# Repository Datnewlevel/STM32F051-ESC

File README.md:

# Single ESC

An open-source hardware learning project for a three-phase electronic speed controller (ESC), designed in KiCad. I created this schematic and PCB while studying existing ESC circuits shared online to understand how their power supply, gate driver, motor bridge, and sensing stages work together.

This is the first PCB revision. I am currently ordering the board for fabrication; the hardware has not yet been assembled or tested.

---

## 1. Overview

The design combines a microcontroller, a three-phase gate driver, six power MOSFETs, and voltage and current sensing on a four-layer PCB. The schematic labels the intended battery input range as 14-25 V. This range is a design target, not a verified operating specification.

The main parts are:

| Function | Component |
|---|---|
| Microcontroller | STM32F051K8U7 |
| Three-phase gate driver | DRV8300DPWR |
| Motor bridge | Six PSMN1R4-40YLDX-VB MOSFETs |
| 3.3 V and 12 V supplies | Two TPS62932DRLR buck converters |
| Current measurement | INA180B2IDBVT amplifier and a 1 mΩ shunt |

The schematic also includes back-EMF sensing for the three motor phases, SWD programming pads, a signal input, telemetry connections, and test pads.

---

## 2. Schematic

The full schematic is available as a [PDF](ESC_PCB/test.pdf). It is divided into the power supplies, microcontroller, gate driver, back-EMF sensing, MOSFET bridge, connectors, and current-sensing sections.

---

## 3. PCB Design

The board is approximately 66.05 × 61.80 mm, with four copper layers and a 1.6 mm board thickness in the KiCad project.

### Top Layer

### GND Plane (Inner Layer 1)

### PWR Plane (Inner Layer 2)

### Bottom Layer

### 3D View

---

## 4. Project Files

| File / Folder | Description |
|---|---|
| `test.kicad_pro` | Main KiCad project settings |
| `test.kicad_sch` | Single ESC schematic source |
| `test.kicad_pcb` | Four-layer PCB layout source |
| `ESC_PCB/` | Schematic PDF and PCB images |
| `production/bom.csv` | Generated bill of materials |
| `production/positions.csv` | Generated component placement data |
| `production/designators.csv` | Generated designator list |
| `production/netlist.ipc` | Generated IPC netlist |
| `production/test.zip` | Generated Gerber and drill files |
| `test/` | A separate KiCad experiment; it is not part of the ESC design |

---

## 5. Current Status

The PCB is being ordered for the first prototype. Assembly, power-up checks, firmware, and motor testing are still pending. The design and fabrication files are shared for study and review, but the board should not be treated as a tested ESC.

---

## 6. References and Open Source

I drew this circuit while referring to existing ESC schematics and other circuits available on the internet. Those references helped me learn the operating principles of an ESC. I do not claim that every circuit idea in this design is original. Specific source links have not yet been collected; I will add attribution for identifiable references.

I intend to release the complete hardware project as open-source hardware. A formal license has not yet been selected and will be added before the public release.

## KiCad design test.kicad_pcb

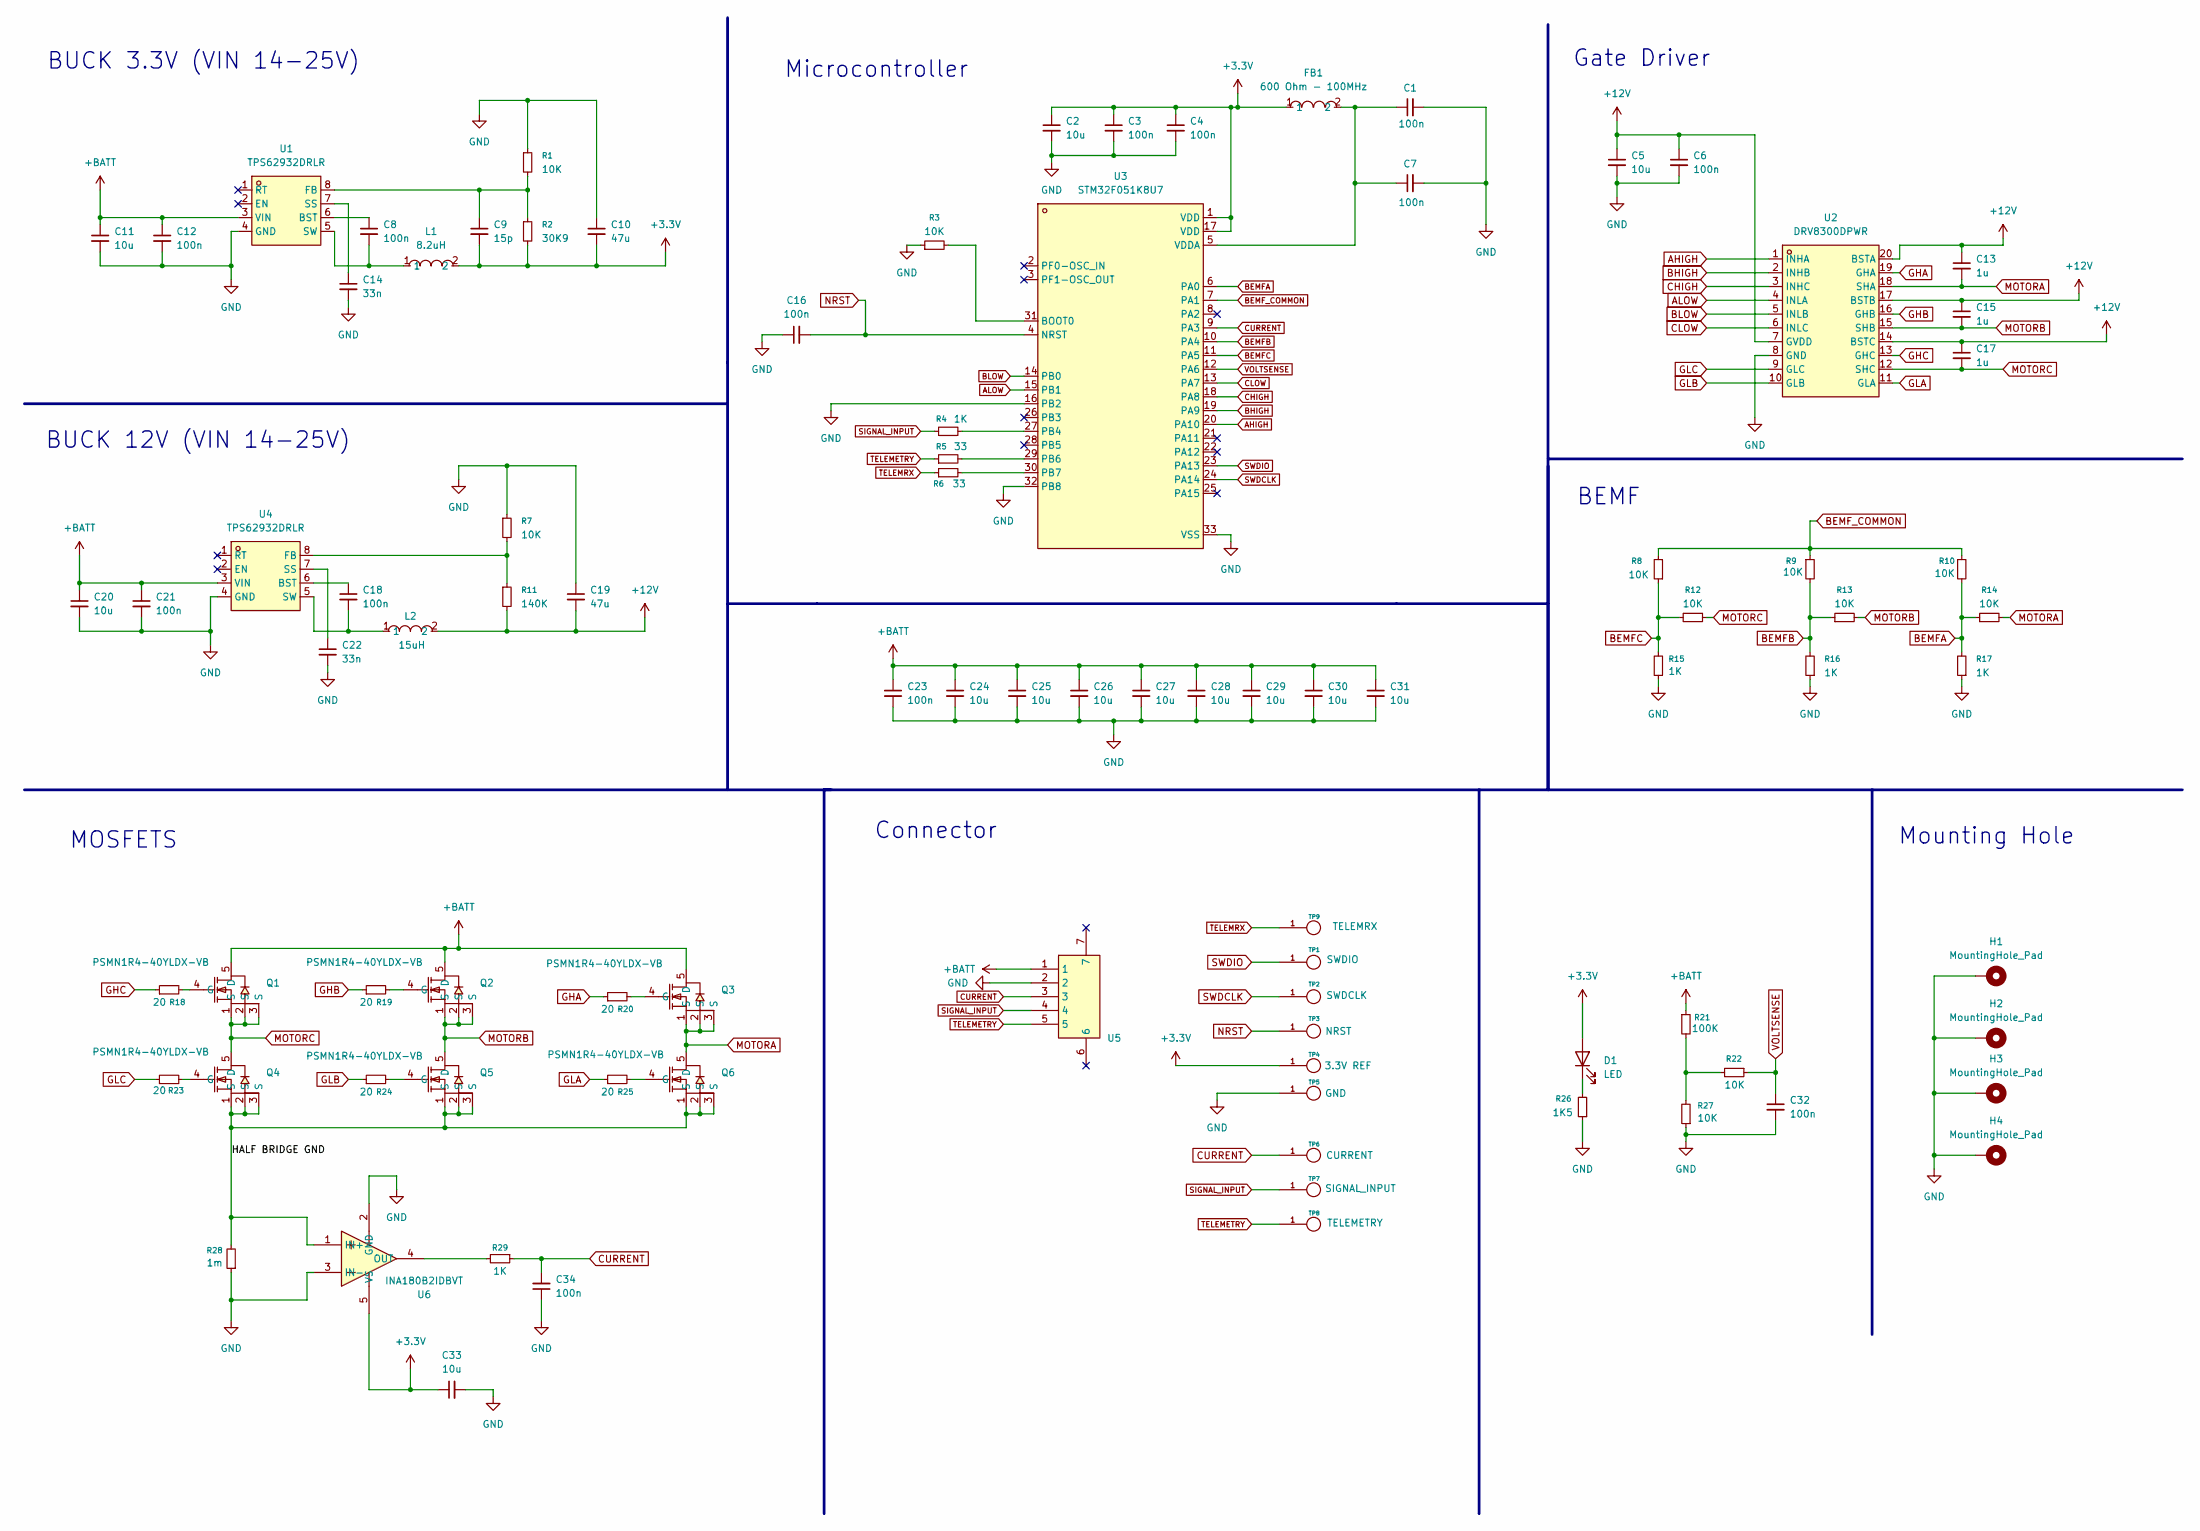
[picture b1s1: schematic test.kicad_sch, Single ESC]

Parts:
C1, C3, C4, C6, C7, C8, C12, C16, C18, C21, C32, C34: 100n; C_0805_2012Metric_Pad1.18x1.45mm_HandSolder
C2, C5, C11, C20, C33: 10u; C_0805_2012Metric_Pad1.18x1.45mm_HandSolder
C9: 15p; C_0805_2012Metric_Pad1.18x1.45mm_HandSolder
C10, C19: 47u; C_1210_3225Metric_Pad1.33x2.70mm_HandSolder
C13, C15, C17: 1u; C_0805_2012Metric_Pad1.18x1.45mm_HandSolder
C14, C22: 33n; C_0805_2012Metric_Pad1.18x1.45mm_HandSolder
C23: 100n; C_1210_3225Metric_Pad1.33x2.70mm_HandSolder
C24, C25, C26, C27, C28, C29, C30, C31: 10u; C_1210_3225Metric_Pad1.33x2.70mm_HandSolder
D1: LED; LED_0805_2012Metric_Pad1.15x1.40mm_HandSolder; LCSC Part C84256
FB1: 600 Ohm - 100MHz; L0603; MPN BLM18KG601SN1D; LCSC Part C85833
H1, H2, H3, H4: MountingHole_Pad; MountingHole_3.2mm_M3_Pad
L1: 8.2uH; IND-SMD_L7.1-W6.6; MPN PSPMAA0603-8R2M-ANF; LCSC Part C436550
L2: 15uH; IND-SMD_L7.1-W6.6; MPN MDA7030-150M; LCSC Part C2847486
Q1, Q2, Q3, Q4, Q5, Q6: PSMN1R4-40YLDX-VB; LFPAK56-4_L4.9-W4.2-P1.27-LS6.2-BL; MPN PSMN1R4-40YLDX-VB; LCSC Part C49253744
R1, R3, R7, R8, R9, R10, R12, R13, R14, R22, R27: 10K; R_0805_2012Metric_Pad1.20x1.40mm_HandSolder; LCSC Part C17414
R2: 30K9; R_0805_2012Metric_Pad1.20x1.40mm_HandSolder; LCSC Part C2933411
R4, R15, R16, R17, R29: 1K; R_0805_2012Metric_Pad1.20x1.40mm_HandSolder; LCSC Part C17513
R5, R6: 33; R_0805_2012Metric_Pad1.20x1.40mm_HandSolder; LCSC Part C17634
R11: 140K; R_0805_2012Metric_Pad1.20x1.40mm_HandSolder; LCSC Part C2933315
R18, R19, R20, R23, R24, R25: 20; R_0805_2012Metric_Pad1.20x1.40mm_HandSolder; LCSC Part C17544
R21: 100K; R_0805_2012Metric_Pad1.20x1.40mm_HandSolder; LCSC Part C149504
R26: 1K5; R_0805_2012Metric_Pad1.20x1.40mm_HandSolder; LCSC Part C2907216
R28: 1m; R2725; LCSC Part C469381
TP1: SWDIO; Flightcontroller_Solder_Pad
TP2: SWDCLK; Flightcontroller_Solder_Pad
TP3: NRST; Flightcontroller_Solder_Pad
TP4: 3.3V REF; Flightcontroller_Solder_Pad
TP5: GND; Flightcontroller_Solder_Pad
TP6: CURRENT; Flightcontroller_Solder_Pad
TP7: SIGNAL_INPUT; Flightcontroller_Solder_Pad
TP8: TELEMETRY; Flightcontroller_Solder_Pad
TP9: TELEMRX; Flightcontroller_Solder_Pad
U1, U4: TPS62932DRLR; SMD-8_L2.1-W1.2-P0.50-LS1.6-BL; MPN TPS62932DRLR; LCSC Part C3032935
U2: DRV8300DPWR; TSSOP-20_L6.5-W4.4-P0.65-LS6.4-BL; MPN DRV8300DPWR; LCSC Part C3036056
U3: STM32F051K8U7; UFQFPN-32_L5.0-W5.0-P0.50-TL-EP3.5; MPN STM32F051K8U7; LCSC Part C2969825
U5: SM05B-GHS-TB; CONN-SMD_5P-P1.25_SM05B-GHS-TB-LF-SN; MPN SM05B-GHS-TB(LF)(SN); LCSC Part C189896
U6: INA180B2IDBVT; SOT-23-5_L2.9-W1.6-P0.95-LS2.8-BR; MPN INA180B2IDBVT; LCSC Part C2058788

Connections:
+3.3V: C2.1, C3.1, C4.1, C9.2, C10.2, C33.1, D1.2 (A), FB1.1, L1.2, R2.2, TP4.1, U3.1 (VDD), U3.17 (VDD), U6.5 (VS)
+12V: C5.1, C6.1, C13.1, C15.1, C17.1, C19.2, L2.2, R11.2, U2.7 (GVDD), U2.14 (BSTC), U2.17 (BSTB), U2.20 (BSTA)
+BATT: C11.1, C12.1, C20.1, C21.1, C23.1, C24.1, C25.1, C26.1, C27.1, C28.1, C29.1, C30.1, C31.1, Q1.5 (D), Q2.5 (D), Q3.5 (D), R21.1, U1.3 (VIN), U4.3 (VIN), U5.1
/HALF BRIDGE GND: Q4.1 (S), Q4.2 (S), Q4.3 (S), Q5.1 (S), Q5.2 (S), Q5.3 (S), Q6.1 (S), Q6.2 (S), Q6.3 (S), R28.2, U6.1 (IN+)
AHIGH: U2.1 (INHA), U3.20 (PA10)
ALOW: U2.4 (INLA), U3.15 (PB1)
BEMFA: R10.2, R14.1, R17.2, U3.6 (PA0)
BEMFB: R9.2, R13.1, R16.2, U3.10 (PA4)
BEMFC: R8.1, R12.2, R15.2, U3.11 (PA5)
BEMF_COMMON: R8.2, R9.1, R10.1, U3.7 (PA1)
BHIGH: U2.2 (INHB), U3.19 (PA9)
BLOW: U2.5 (INLB), U3.14 (PB0)
CHIGH: U2.3 (INHC), U3.18 (PA8)
CLOW: U2.6 (INLC), U3.13 (PA7)
CURRENT: C34.2, R29.1, TP6.1, U3.9 (PA3), U5.3
GHA: R20.1, U2.19 (GHA)
GHB: R19.1, U2.16 (GHB)
GHC: R18.1, U2.13 (GHC)
GLA: R25.1, U2.11 (GLA)
GLB: R24.1, U2.10 (GLB)
GLC: R23.1, U2.9 (GLC)
GND: C1.2, C2.2, C3.2, C4.2, C5.2, C6.2, C7.2, C10.1, C11.2, C12.2, C14.2, C16.1, C19.1, C20.2, C21.2, C22.2, C23.2, C24.2, C25.2, C26.2, C27.2, C28.2, C29.2, C30.2, C31.2, C32.2, C33.2, C34.1, H1.1 (1_1), H2.1 (1_1), H3.1 (1_1), H4.1 (1_1), R1.1, R3.1, R7.1, R15.1, R16.1, R17.1, R26.1, R27.1, R28.1, TP5.1, U1.4 (GND), U2.8 (GND), U3.16 (PB2), U3.32 (PB8), U3.33 (VSS), U4.4 (GND), U5.2, U6.2 (GND), U6.3 (IN-)
MOTORA: C13.2, Q3.1 (S), Q3.2 (S), Q3.3 (S), Q6.5 (D), R14.2, U2.18 (SHA)
MOTORB: C15.2, Q2.1 (S), Q2.2 (S), Q2.3 (S), Q5.5 (D), R13.2, U2.15 (SHB)
MOTORC: C17.2, Q1.1 (S), Q1.2 (S), Q1.3 (S), Q4.5 (D), R12.1, U2.12 (SHC)
NRST: C16.2, TP3.1, U3.4 (NRST)
unnamed: D1.1 (K), R26.2
unnamed: Q1.4 (G), R18.2
unnamed: Q2.4 (G), R19.2
unnamed: Q3.4 (G), R20.2
unnamed: Q4.4 (G), R23.2
unnamed: Q5.4 (G), R24.2
unnamed: Q6.4 (G), R25.2
unnamed: R21.2, R22.2, R27.2
unnamed: C8.1, U1.6 (BST)
unnamed: C9.1, R1.2, R2.1, U1.8 (FB)
unnamed: C14.1, U1.7 (SS)
unnamed: C8.2, L1.1, U1.5 (SW)
unnamed: R3.2, U3.31 (BOOT0)
unnamed: R4.2, U3.27 (PB4)
unnamed: R5.2, U3.29 (PB6)
unnamed: R6.2, U3.30 (PB7)
unnamed: C1.1, C7.1, FB1.2, U3.5 (VDDA)
unnamed: C18.1, U4.6 (BST)
unnamed: R7.2, R11.1, U4.8 (FB)
unnamed: C22.1, U4.7 (SS)
unnamed: C18.2, L2.1, U4.5 (SW)
unnamed: R29.2, U6.4 (OUT)
SIGNAL_INPUT: R4.1, TP7.1, U5.4
SWDCLK: TP2.1, U3.24 (PA14)
SWDIO: TP1.1, U3.23 (PA13)
TELEMETRY: R5.1, TP8.1, U5.5
TELEMRX: R6.1, TP9.1
VOLTSENSE: C32.1, R22.1, U3.12 (PA6)

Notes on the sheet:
Gate Driver
MOSFETS
BEMF
Connector
BUCK 12V (VIN 14-25V)
Mounting Hole
Microcontroller
BUCK 3.3V (VIN 14-25V)

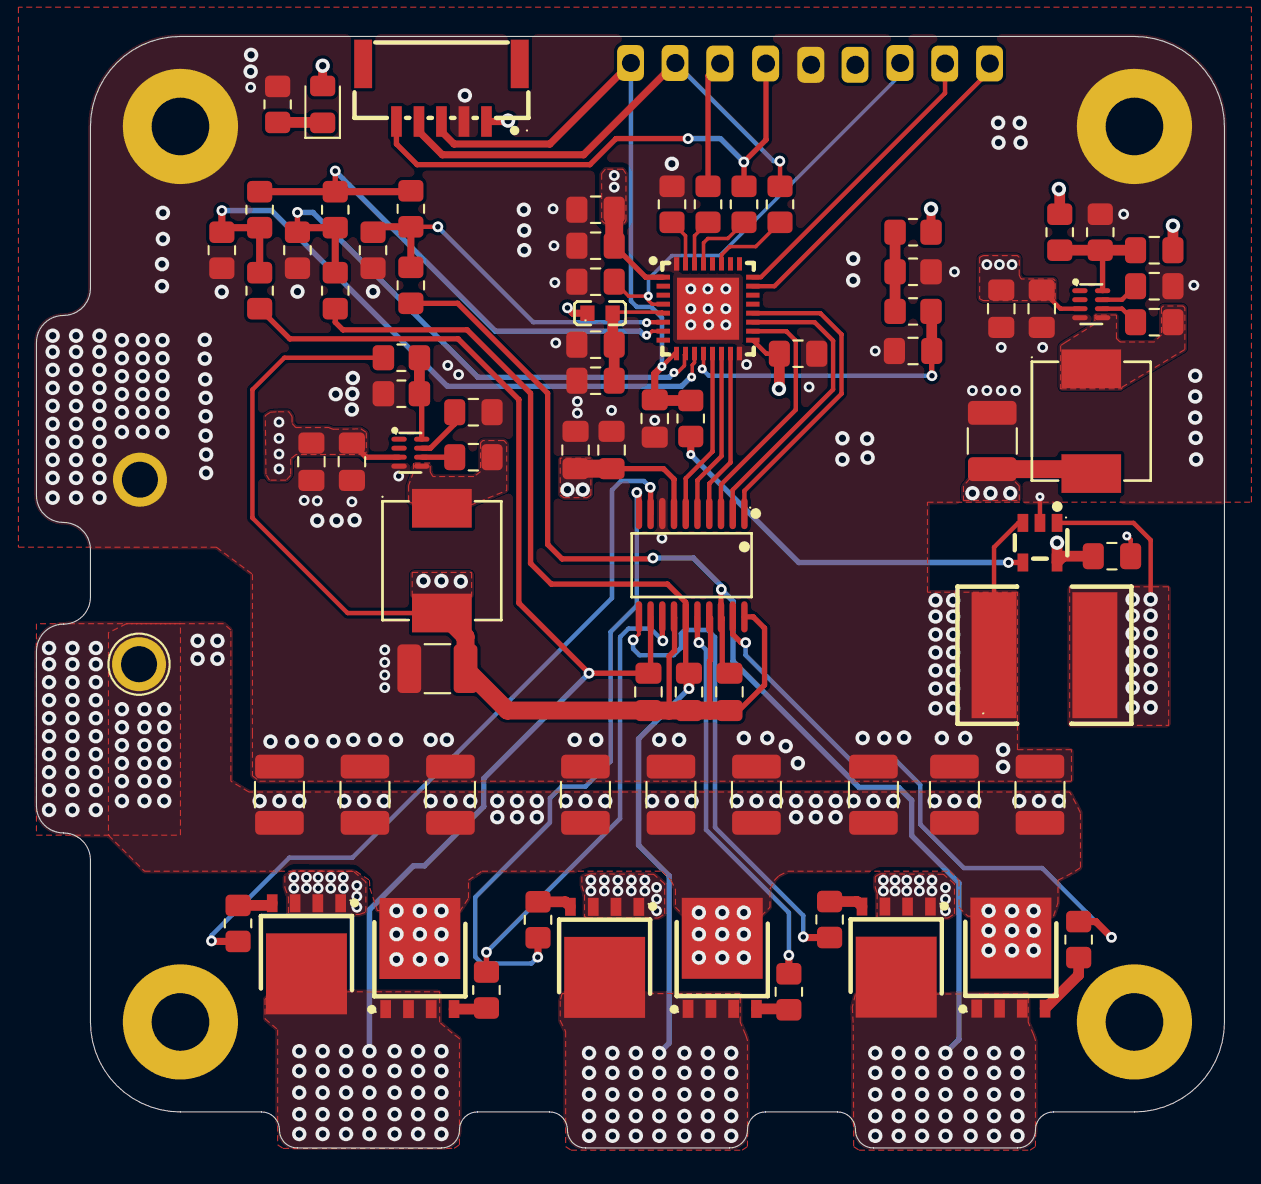
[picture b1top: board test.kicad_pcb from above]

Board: 4 copper layers, 66.0 x 61.8 mm, 92 parts (0 on the bottom side), 54 nets.

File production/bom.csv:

Designator,Footprint,Quantity,Value,LCSC Part #
,,1,,
"C1, C12, C16, C18, C21, C3, C32, C34, C4, C6, C7, C8",805,12,100n,
"C10, C19",1210,2,47u,
"C11, C2, C20, C33, C5",805,5,10u,
"C13, C15, C17",805,3,1u,
"C14, C22",805,2,33n,
C23,1210,1,100n,
"C24, C25, C26, C27, C28, C29, C30, C31",1210,8,10u,
C9,805,1,15p,
D1,805,1,LED,
FB1,L0603,1,600 Ohm - 100MHz,C85833
L1,IND-SMD_L7.1-W6.6,1,8.2uH,C436550
L2,IND-SMD_L7.1-W6.6,1,15uH,C2847486
"Q1, Q2, Q3, Q4, Q5, Q6",LFPAK56-4_L4.9-W4.2-P1.27-LS6.2-BL,6,PSMN1R4-40YLDX-VB,C49253744
"R1, R10, R12, R13, R14, R22, R27, R3, R7, R8, R9",805,11,10K,
R11,805,1,140K,
"R15, R16, R17, R29, R4",805,5,1K,
"R18, R19, R20, R23, R24, R25",805,6,20,
R2,805,1,30K9,
R21,805,1,100K,
R26,805,1,1K5,
R28,R2725,1,1m,C469381
"R5, R6",805,2,33,
"U1, U4",SMD-8_L2.1-W1.2-P0.50-LS1.6-BL,2,TPS62932DRLR,C3032935
U2,TSSOP-20_L6.5-W4.4-P0.65-LS6.4-BL,1,DRV8300DPWR,C3036056
U3,UFQFPN-32_L5.0-W5.0-P0.50-TL-EP3.5,1,STM32F051K8U7,C2969825
U5,CONN-SMD_5P-P1.25_SM05B-GHS-TB-LF-SN,1,SM05B-GHS-TB,C189896
U6,SOT-23-5_L2.9-W1.6-P0.95-LS2.8-BR,1,INA180B2IDBVT,C2058788
